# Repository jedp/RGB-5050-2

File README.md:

# Yet Another RGB5050 Mount

A chainable board for mounting addressable [RGB 5050
LED](https://www.digikey.com/en/products/detail/inolux/IN-PI554FCH/7604874)s to things.

## BOM

- [5050
  LED](https://www.digikey.com/en/products/detail/inolux/IN-PI554FCH/7604874)
- 0.1μF 0805 ceramic capacitor

## Bit-banging

These high-speed LEDs deal in ones and zeros at microsecond speed. One way to get this
kind of speed out of an STM32 without tying up the CPU and/or writing a lot of custom
assembly is to use SPI to transmit the data, possibly using DMA to send the data to SPI.

The RGB5050 encodes 0 and 1 values as high/low transitions like so:

```
0 -> 0.3µs high ± 0.15µs, 0.9µs low ± 0.15µs
1 -> 0.6µs high ± 0.15µs, 0.6µs low ± 0.15µs
```

My first attempt was to try a transfer rate of 2.5Mbps, since this would
require the minimum number of encoded output bits (0 -> 0b100, 1 -> 0b110).
This is obviously out of spec for the timings. It was worth a go, bit it didn't
work reliably.

Bumping the transfer rate to 5Mbps doubles the number of bits required, but
has the benefit of actually working:

```
0 -> 0b100000 (0.2µs high, 1.0µs low)
1 -> 0b111000 (0.6µs high, 0.6µs low)
```

To implement this, one could iterate over each source byte of and do some fancy
bit arithmetic for every single byte (see previous commit), or one could follow
the advice of the mighty Ross Glashan and just use a lookup table, since there
are only 16 possible encodings of each nibble.

For example:

```
static uint32_t color_nibbles[16] = {
		0x820820, // 0b0000 -> 0b100000100000100000100000
		0x820838, // 0b0001 -> 0b100000100000100000111000
		0x820e20, // 0b0010 -> 0b100000100000111000100000
		0x820e38, // etc.
		0x838820,
		0x838838,
		0x838e20,
		0x838e38,
		0xe20820,
		0xe20838,
		0xe20e20,
		0xe20e38,
		0xe38820,
		0xe38838,
		0xe38e20,
		0xe38e38, // 0b1111 -> 0b111000111000111000111000
};

/*
 * Convert the pixel represented by (r, g, b), using the scheme described
 * at the head of this file, and pack it into buf in RGB 5050 order:
 * G, R, B; MSB first.
 */
void RGB5050_pixel_write(uint8_t r, uint8_t g, uint8_t b, uint8_t *buf) {
	// For each nibble of r, g, b, get the 24-bit output encoding of that nibble.
	uint32_t r_high = color_nibbles[r >> 4];
	uint32_t r_low  = color_nibbles[r & 0xf];
	uint32_t g_high = color_nibbles[g >> 4];
	uint32_t g_low  = color_nibbles[g & 0xf];
	uint32_t b_high = color_nibbles[b >> 4];
	uint32_t b_low  = color_nibbles[b & 0xf];

	buf[0]  = (g_high >> 16) & 0xff;
	buf[1]  = (g_high >>  8) & 0xff;
	buf[2]  = (g_high)       & 0xff;
	buf[3]  = (g_low  >> 16) & 0xff;
	buf[4]  = (g_low  >>  8) & 0xff;
	buf[5]  = (g_low)        & 0xff;

	buf[6]  = (r_high >> 16) & 0xff;
	buf[7]  = (r_high >>  8) & 0xff;
	buf[8]  = (r_high)       & 0xff;
	buf[9]  = (r_low  >> 16) & 0xff;
	buf[10] = (r_low  >>  8) & 0xff;
	buf[11] = (r_low)        & 0xff;

	buf[12] = (b_high >> 16) & 0xff;
	buf[13] = (b_high >>  8) & 0xff;
	buf[14] = (b_high)       & 0xff;
	buf[15] = (b_low  >> 16) & 0xff;
	buf[16] = (b_low  >>  8) & 0xff;
	buf[17] = (b_low)        & 0xff;
}
```

So you could set a region of a buffer like this:
```
RGB5050_pixel_write(0xAB, 0xCD, 0xEF, (uint8_t*) (some_buffer + 18 * offset));
```

And then transmit that buffer over SPI:
```
HAL_SPI_Transmit(&hspi1, (uint8_t*) some_buffer, sizeof(some_buffer), 1);
```

After transmission, leave a reset cycle of at least 80µs before transmitting again.

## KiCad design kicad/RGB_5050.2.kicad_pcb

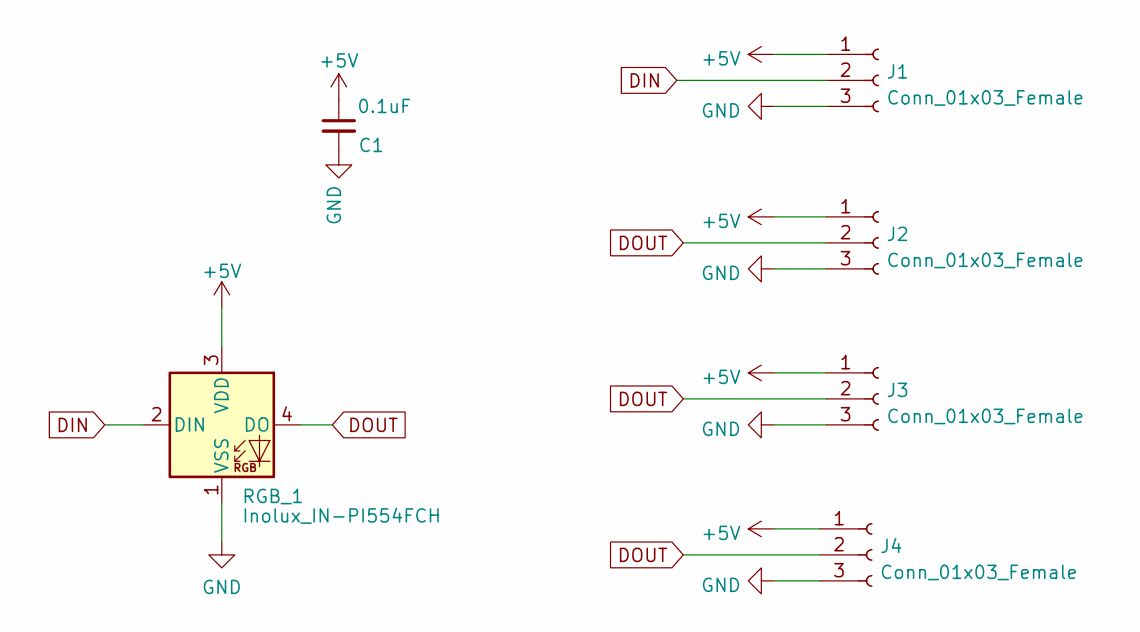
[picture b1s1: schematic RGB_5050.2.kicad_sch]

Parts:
C1: 0.1uF; C_0805_2012Metric
J1, J2, J3, J4: Conn_01x03_Female; PinHeader_1x03_P2.54mm_Vertical
RGB_1: Inolux_IN-PI554FCH; LED_Inolux_IN-PI554FCH_PLCC4_5.0x5.0mm_P3.2mm

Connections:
+5V: C1.1, J1.1, J2.1, J3.1, J4.1, RGB_1.3 (VDD)
DIN: J1.2, RGB_1.2 (DIN)
DOUT: J2.2, J3.2, J4.2, RGB_1.4 (DO)
GND: C1.2, J1.3, J2.3, J3.3, J4.3, RGB_1.1 (VSS)

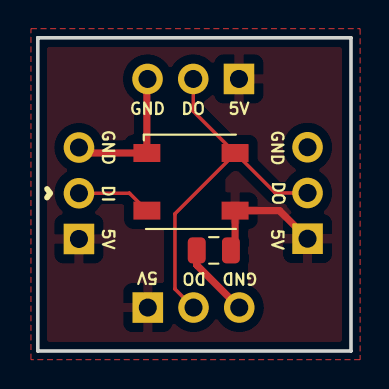
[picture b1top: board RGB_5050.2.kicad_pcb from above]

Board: 2 copper layers, 17.4 x 17.4 mm, 6 parts (0 on the bottom side), 4 nets.

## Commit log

2022-09-11 v1 adjustments
2023-12-30 Recipe for bit-banging with SPI
2024-01-02 Lookup table is fast
